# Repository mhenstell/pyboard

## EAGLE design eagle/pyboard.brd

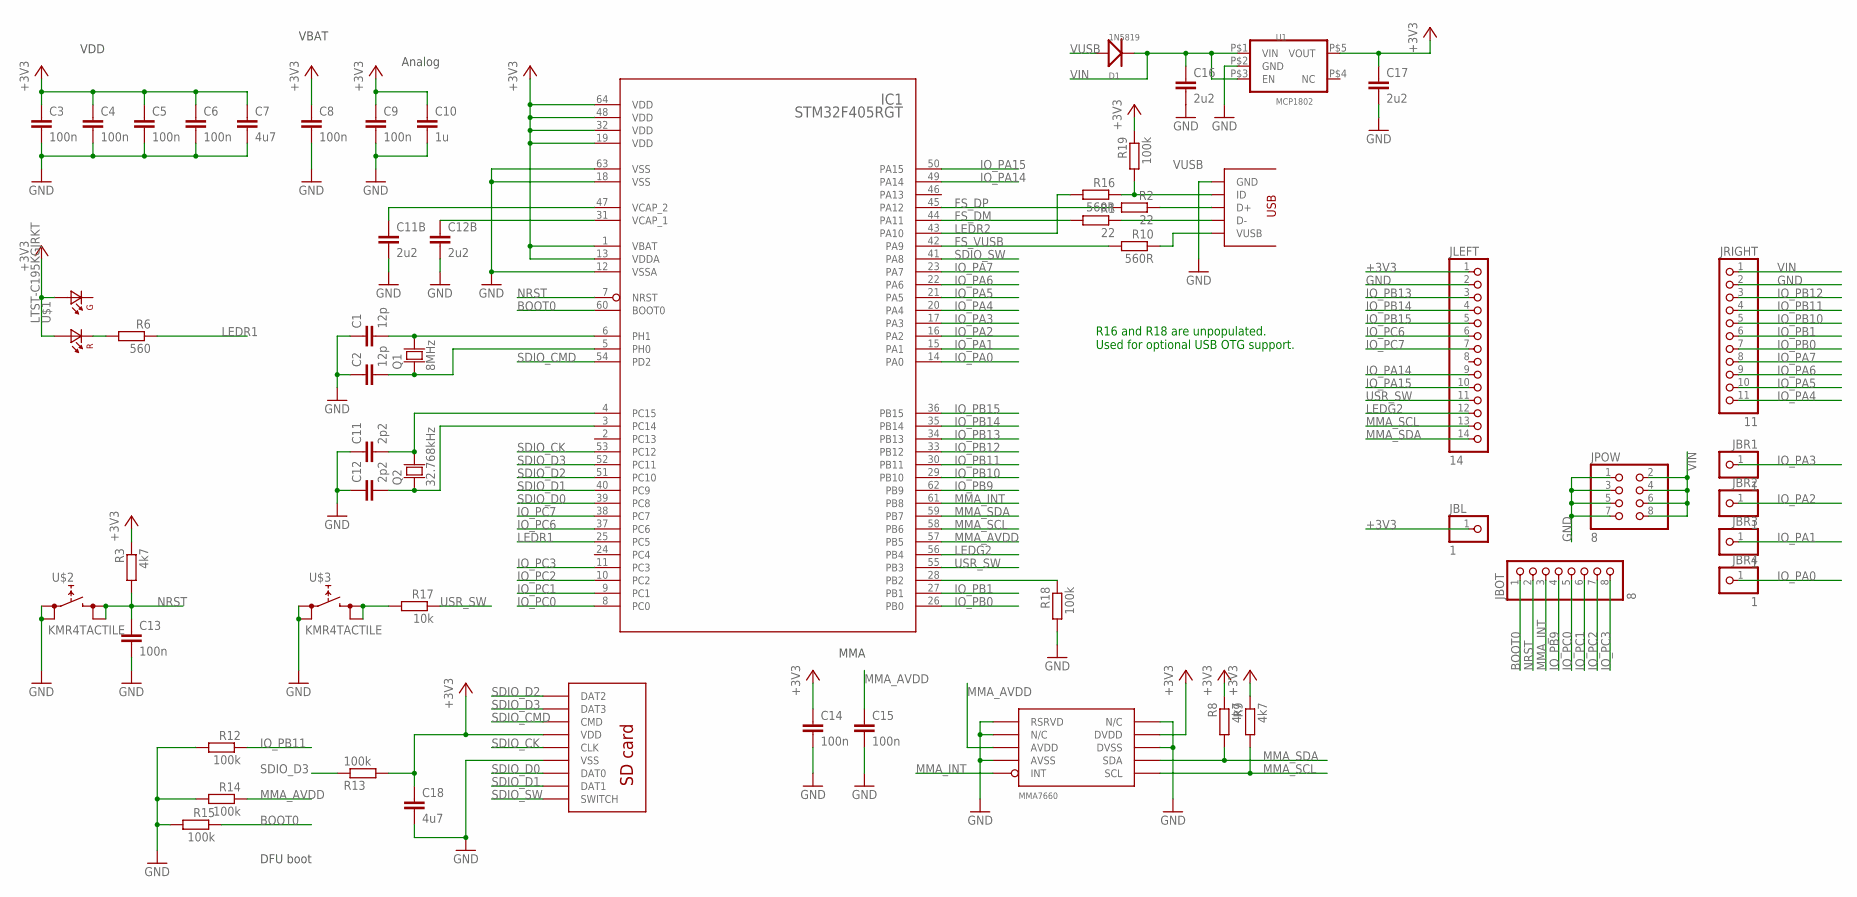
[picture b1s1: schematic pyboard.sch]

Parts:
C1, C2: 12p; C0603; PARTNO CL10C120JB8NNNC
C3, C4, C5, C6, C8, C9, C13, C14, C15: 100n; C0603; PARTNO C0603C104J4RACTU
C7, C18: 4u7; C0603; PARTNO CL10B475KQ8NQNC
C10: 1u; C0603; PARTNO YNA18B2C0G105M
C11, C12: 2p2; C0603; PARTNO CL10C2R2CB8NNNC
C11B, C12B, C16, C17: 2u2; C0603; PARTNO LMK107B7225KA-T
D1: 1N5819; SOD-123; PARTNO 1N5819HW-7-F
IC1: STM32F405RGT; LQFP64; PARTNO STM32F405RGT6
JBL: 1; 1X01
JBOT: 8; 1X08
JBR1, JBR2, JBR3, JBR4: 1; 1X01
JLEFT: 14; 1X14
JPOW: 8; 2X04
JRIGHT: 11; 1X11
Q1: 8MHz; TXC-SMD-50X32; PARTNO AA-8.000MALV-T
Q2: 32.768kHz; TXC-SMD-32X15; PARTNO ABS07-120-32.768KHZ-T
R1, R2: 22; R0603; PARTNO MCR03ERTJ220
R3, R8, R9: 4k7; R0603; PARTNO RC0603JR-074K7L
R6: 560; R0603; PARTNO RC0603FR-07560RL
R10, R16: 560R; R0603; PARTNO RC0603FR-07560RL
R12, R13, R14, R15, R18, R19: 100k; R0603; PARTNO RC0603JR-07100KL
R17: 10k; R0603; PARTNO RC0603JR-0710KL
U1: MCP1802; SOT-23-5; PARTNO MCP1802T-3302I/OT
U$1: LTST-C195KGJRKT; LTST-BILED-15X16; PARTNO LTST-C195KGJRKT
U$2, U$3: KMR4TACTILE; KMR4SWITCH; PARTNO KMR442G LFS
U$4: MOLEX-SD-105027; MOLEX-SD-105027-PKG; PARTNO 1050270001
U$5: MMA7660; DFN10; PARTNO MMA7660FCR1
U$7: USB-MICRO-AB; HRS-USB-ZX62D-AB-5P8-PKG; PARTNO ZX62D-AB-5P8

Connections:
+3V3: C3.1, C4.1, C5.1, C6.1, C7.1, C8.1, C9.1, C10.1, C14.1, C17.1, C18.1, IC1.1 (VBAT), IC1.13 (VDDA), IC1.19 (VDD), IC1.32 (VDD), IC1.48 (VDD), IC1.64 (VDD), JBL.1, JLEFT.1, R3.1, R8.1, R9.1, R13.2, R19.1, U1.P$5 (VOUT), U$1.P$1 (A1), U$1.P$2 (A2), U$4.P$4 (VDD), U$5.P$9 (DVDD)
BOOT0: IC1.60 (BOOT0), JBOT.1, R15.1
FS_DM: IC1.44 (PA11), R1.2
FS_DP: IC1.45 (PA12), R2.2
FS_VUSB: IC1.42 (PA9), R10.2
GND: C1.1, C2.1, C3.2, C4.2, C5.2, C6.2, C7.2, C8.2, C9.2, C10.2, C11.1, C11B.2, C12.1, C12B.2, C13.2, C14.2, C15.2, C16.2, C17.2, C18.2, IC1.12 (VSSA), IC1.18 (VSS), IC1.63 (VSS), JLEFT.2, JPOW.1, JPOW.3, JPOW.5, JPOW.7, JRIGHT.2, R12.2, R14.2, R15.2, R18.2, U1.P$2 (GND), U$2.P$1 (0), U$2.P$2 (0), U$3.P$1 (0), U$3.P$2 (0), U$4.P$6 (VSS), U$5.P$1 (RSRVD), U$5.P$2 (N/C), U$5.P$4 (AVSS), U$5.P$8 (DVSS), U$5.P$10 (N/C), U$7.P$5 (GND)
IO_PA0: IC1.14 (PA0), JBR4.1
IO_PA1: IC1.15 (PA1), JBR3.1
IO_PA2: IC1.16 (PA2), JBR2.1
IO_PA3: IC1.17 (PA3), JBR1.1
IO_PA4: IC1.20 (PA4), JRIGHT.11
IO_PA5: IC1.21 (PA5), JRIGHT.10
IO_PA6: IC1.22 (PA6), JRIGHT.9
IO_PA7: IC1.23 (PA7), JRIGHT.8
IO_PA14: IC1.49 (PA14), JLEFT.9
IO_PA15: IC1.50 (PA15), JLEFT.10
IO_PB0: IC1.26 (PB0), JRIGHT.7
IO_PB1: IC1.27 (PB1), JRIGHT.6
IO_PB9: IC1.62 (PB9), JBOT.4
IO_PB10: IC1.29 (PB10), JRIGHT.5
IO_PB11: IC1.30 (PB11), JRIGHT.4, R12.1
IO_PB12: IC1.33 (PB12), JRIGHT.3
IO_PB13: IC1.34 (PB13), JLEFT.3
IO_PB14: IC1.35 (PB14), JLEFT.4
IO_PB15: IC1.36 (PB15), JLEFT.5
IO_PC0: IC1.8 (PC0), JBOT.5
IO_PC1: IC1.9 (PC1), JBOT.6
IO_PC2: IC1.10 (PC2), JBOT.7
IO_PC3: IC1.11 (PC3), JBOT.8
IO_PC6: IC1.37 (PC6), JLEFT.6
IO_PC7: IC1.38 (PC7), JLEFT.7
LEDG2: IC1.56 (PB4), JLEFT.12
LEDR1: IC1.25 (PC5), R6.1
LEDR2: IC1.43 (PA10), R16.2
MMA_AVDD: C15.1, IC1.57 (PB5), R14.1, U$5.P$3 (AVDD)
MMA_INT: IC1.61 (PB8), JBOT.3, U$5.P$5 (INT)
MMA_SCL: IC1.58 (PB6), JLEFT.13, R9.2, U$5.P$6 (SCL)
MMA_SDA: IC1.59 (PB7), JLEFT.14, R8.2, U$5.P$7 (SDA)
unnamed: C11B.1, IC1.47 (VCAP_2)
unnamed: C12B.1, IC1.31 (VCAP_1)
unnamed: R2.1, U$7.P$3 (D+)
unnamed: R1.1, U$7.P$2 (D-)
unnamed: C12.2, IC1.3 (PC14), Q2.P$1
unnamed: C11.2, IC1.4 (PC15), Q2.P$2
unnamed: R16.1, R19.2, U$7.P$4 (ID)
unnamed: IC1.28 (PB2), R18.1
unnamed: C1.2, IC1.6 (PH1), Q1.P$2
unnamed: C2.2, IC1.5 (PH0), Q1.P$1
unnamed: R6.2, U$1.P$4 (K2)
unnamed: R17.2, U$3.P$3 (1), U$3.P$4 (1)
NRST: C13.1, IC1.7 (NRST), JBOT.2, R3.2, U$2.P$3 (1), U$2.P$4 (1)
SDIO_CK: IC1.53 (PC12), U$4.P$5 (CLK)
SDIO_CMD: IC1.54 (PD2), U$4.P$3 (CMD)
SDIO_D0: IC1.39 (PC8), U$4.P$7 (DAT0)
SDIO_D1: IC1.40 (PC9), U$4.P$8 (DAT1)
SDIO_D2: IC1.51 (PC10), U$4.P$1 (DAT2)
SDIO_D3: IC1.52 (PC11), R13.1, U$4.P$2 (DAT3)
SDIO_SW: IC1.41 (PA8), U$4.G$1 (SWITCH)
USR_SW: IC1.55 (PB3), JLEFT.11, R17.1
VIN: C16.1, D1.K, JPOW.2, JPOW.4, JPOW.6, JPOW.8, JRIGHT.1, U1.P$1 (VIN), U1.P$3 (EN)
VUSB: D1.A, R10.1, U$7.P$1 (VUSB)

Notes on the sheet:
Analog
DFU boot
MMA
VBAT
VDD
R16 and R18 are unpopulated. Used for optional USB OTG support.

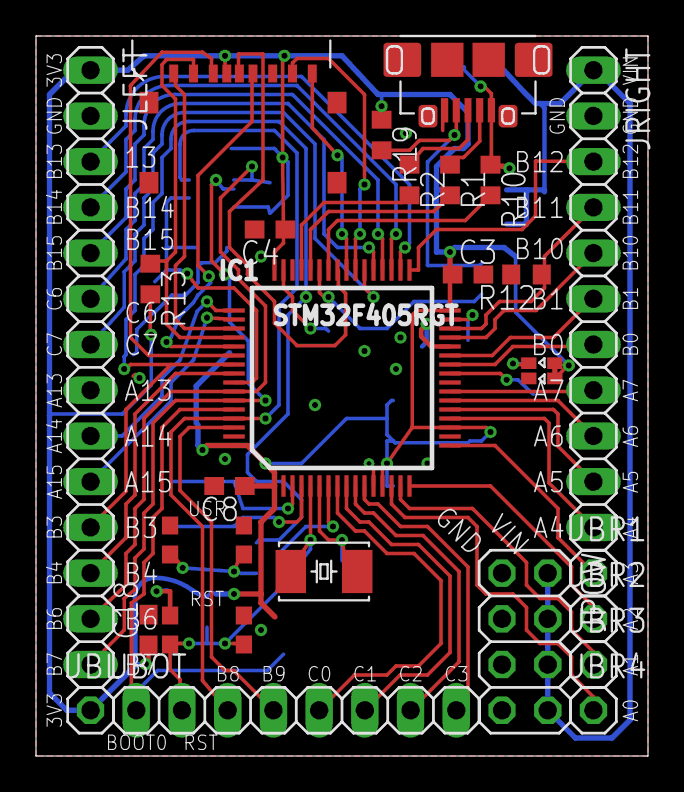
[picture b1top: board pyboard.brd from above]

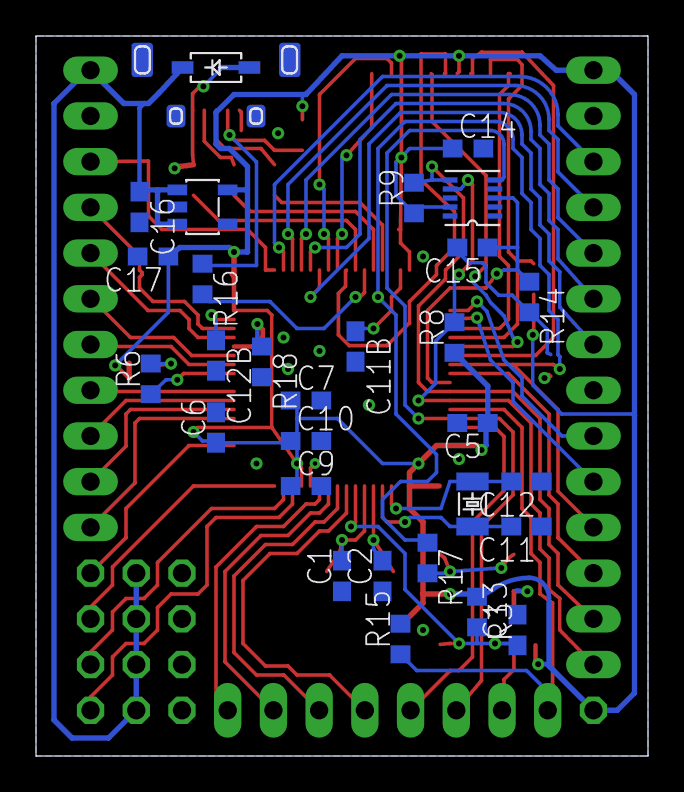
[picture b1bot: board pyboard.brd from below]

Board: 2 copper layers, 34.0 x 40.0 mm, 55 parts (29 on the bottom side), 61 nets.

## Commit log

2014-07-15 updated pyboard to more closely resemble the newer v10 boards for which eagle files aren't available yet
2014-09-26 changes from laptop
2014-09-26 old computer changes, double check
